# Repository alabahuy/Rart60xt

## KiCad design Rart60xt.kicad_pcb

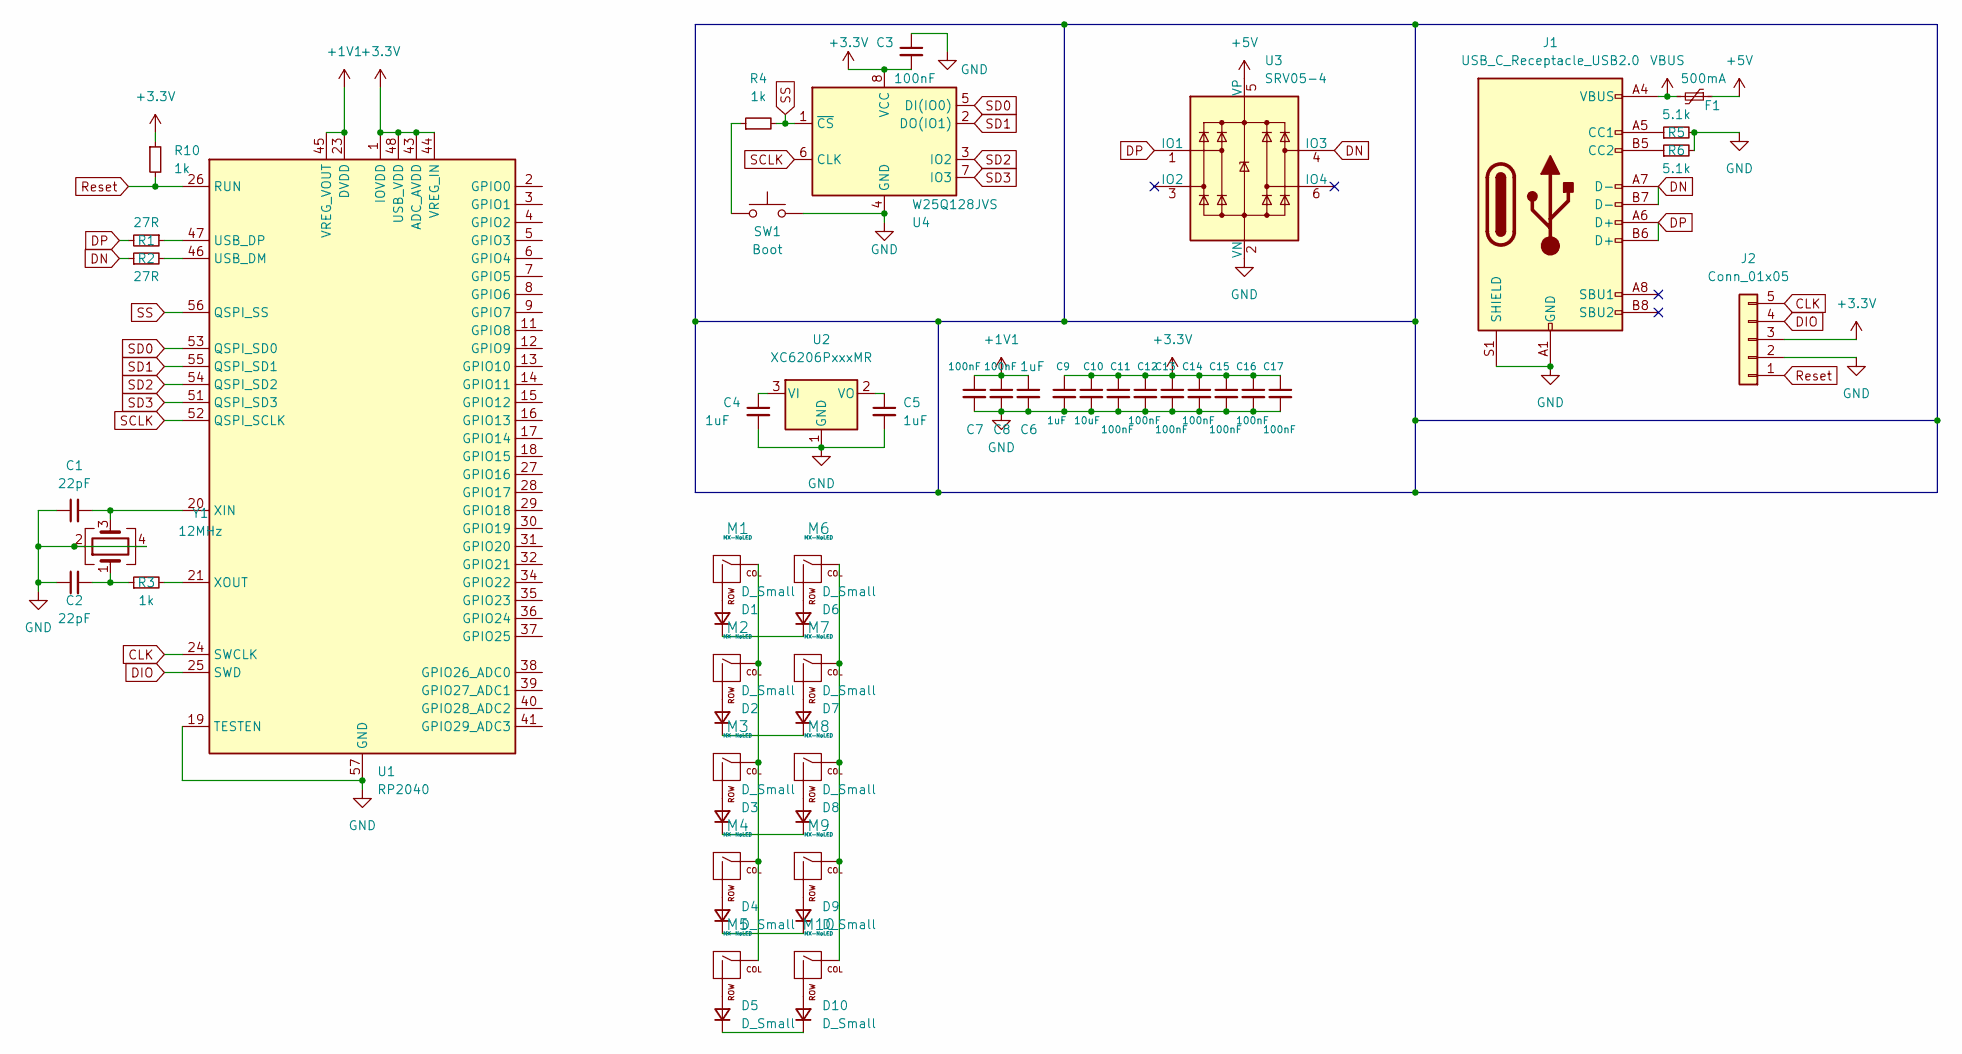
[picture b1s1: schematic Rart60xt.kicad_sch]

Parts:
C1, C2: 22pF; C_0805_2012Metric
C3, C7, C8, C11, C12, C13, C14, C15, C16, C17: 100nF; C_0805_2012Metric
C4, C5, C6, C9: 1uF; C_0805_2012Metric
C10: 10uF; C_0805_2012Metric
D1, D2, D3, D4, D5, D6, D7, D8, D9, D10: D_Small; D_SOD-123
F1: 500mA; Fuse_1206_3216Metric
J1: USB_C_Receptacle_USB2.0; USB_C_Receptacle_HRO_TYPE-C-31-M-12
J2: Conn_01x05; PinHeader_1x05_P2.00mm_Vertical
M1, M2, M3, M4, M5, M6, M7, M8, M9, M10: MX-NoLED; SW_Cherry_MX_1.00u_PCB
R1, R2: 27R; R_0805_2012Metric
R3, R4, R10: 1k; R_0805_2012Metric
R5, R6: 5.1k; R_0805_2012Metric
SW1: Boot; Reset_Pretty
U1: RP2040; QFN-56-1EP_7x7mm_P0.4mm_EP3.2x3.2mm
U2: XC6206PxxxMR; SOT-23
U3: SRV05-4; SOT-23-6
U4: W25Q128JVS; SOIC-8_5.23x5.23mm_P1.27mm
Y1: 12MHz; Crystal_SMD_3225-4Pin_3.2x2.5mm

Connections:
+1V1: C6.1, C7.1, C8.1, U1.23 (DVDD), U1.45 (VREG_VOUT), U1.50 (DVDD)
+3.3V: C3.2, C9.1, C10.1, C11.1, C12.1, C13.1, C14.1, C15.1, C16.1, C17.1, J2.3, R10.1, U1.1 (IOVDD), U1.10 (IOVDD), U1.22 (IOVDD), U1.33 (IOVDD), U1.42 (IOVDD), U1.43 (ADC_AVDD), U1.44 (VREG_IN), U1.48 (USB_VDD), U1.49 (IOVDD), U4.8 (VCC)
+5V: F1.1, U3.5 (VP)
CLK: J2.5, U1.24 (SWCLK)
DIO: J2.4, U1.25 (SWD)
DN: J1.A7 (D-), J1.B7 (D-), R2.1, U3.4 (IO3)
DP: J1.A6 (D+), J1.B6 (D+), R1.2, U3.1 (IO1)
GND: C1.1, C2.1, C3.1, C4.2, C5.2, C6.2, C7.2, C8.2, C9.2, C10.2, C11.2, C12.2, C13.2, C14.2, C15.2, C16.2, C17.2, J1.A1 (GND), J1.A12 (GND), J1.B1 (GND), J1.B12 (GND), J1.S1 (SHIELD), J2.2, R5.2, R6.2, SW1.2, U1.19 (TESTEN), U1.57 (GND), U2.1 (GND), U3.2 (VN), U4.4 (GND), Y1.2, Y1.4
unnamed: C1.2, U1.20 (XIN), Y1.3
unnamed: C2.2, R3.1, Y1.1
unnamed: C4.1, U2.3 (VI)
unnamed: C5.1, U2.2 (VO)
unnamed: D1.1 (K), D6.1 (K)
unnamed: D2.1 (K), D7.1 (K)
unnamed: D3.1 (K), D8.1 (K)
unnamed: D4.1 (K), D9.1 (K)
unnamed: D5.1 (K), D10.1 (K)
unnamed: D6.2 (A), M6.2 (ROW)
unnamed: D7.2 (A), M7.2 (ROW)
unnamed: D8.2 (A), M8.2 (ROW)
unnamed: D9.2 (A), M9.2 (ROW)
unnamed: D10.2 (A), M10.2 (ROW)
unnamed: J1.A5 (CC1), R5.1
unnamed: J1.B5 (CC2), R6.1
unnamed: M1.1 (COL), M2.1 (COL), M3.1 (COL), M4.1 (COL), M5.1 (COL)
unnamed: D1.2 (A), M1.2 (ROW)
unnamed: D2.2 (A), M2.2 (ROW)
unnamed: D3.2 (A), M3.2 (ROW)
unnamed: D4.2 (A), M4.2 (ROW)
unnamed: D5.2 (A), M5.2 (ROW)
unnamed: M6.1 (COL), M7.1 (COL), M8.1 (COL), M9.1 (COL), M10.1 (COL)
unnamed: R1.1, U1.47 (USB_DP)
unnamed: R2.2, U1.46 (USB_DM)
unnamed: R3.2, U1.21 (XOUT)
unnamed: R4.1, SW1.1
Reset: J2.1, R10.2, U1.26 (RUN)
SCLK: U1.52 (QSPI_SCLK), U4.6 (CLK)
SD0: U1.53 (QSPI_SD0), U4.5 (DI(IO0))
SD1: U1.55 (QSPI_SD1), U4.2 (DO(IO1))
SD2: U1.54 (QSPI_SD2), U4.3 (IO2)
SD3: U1.51 (QSPI_SD3), U4.7 (IO3)
SS: R4.2, U1.56 (QSPI_SS), U4.1 (~CS)
VBUS: F1.2, J1.A4 (VBUS), J1.A9 (VBUS), J1.B4 (VBUS), J1.B9 (VBUS)

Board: 2 copper layers, 53 parts (0 on the bottom side), 43 nets, no tracks yet.

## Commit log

2022-08-16 add submodules
2022-08-16 Add Submodule
2022-08-16 resume
2022-08-16 Process
2022-08-16 break
2022-08-21 done
2022-09-07 add DB
2022-09-22 addadda
2022-11-01 addadd
2023-01-04 Update 75.b#1
